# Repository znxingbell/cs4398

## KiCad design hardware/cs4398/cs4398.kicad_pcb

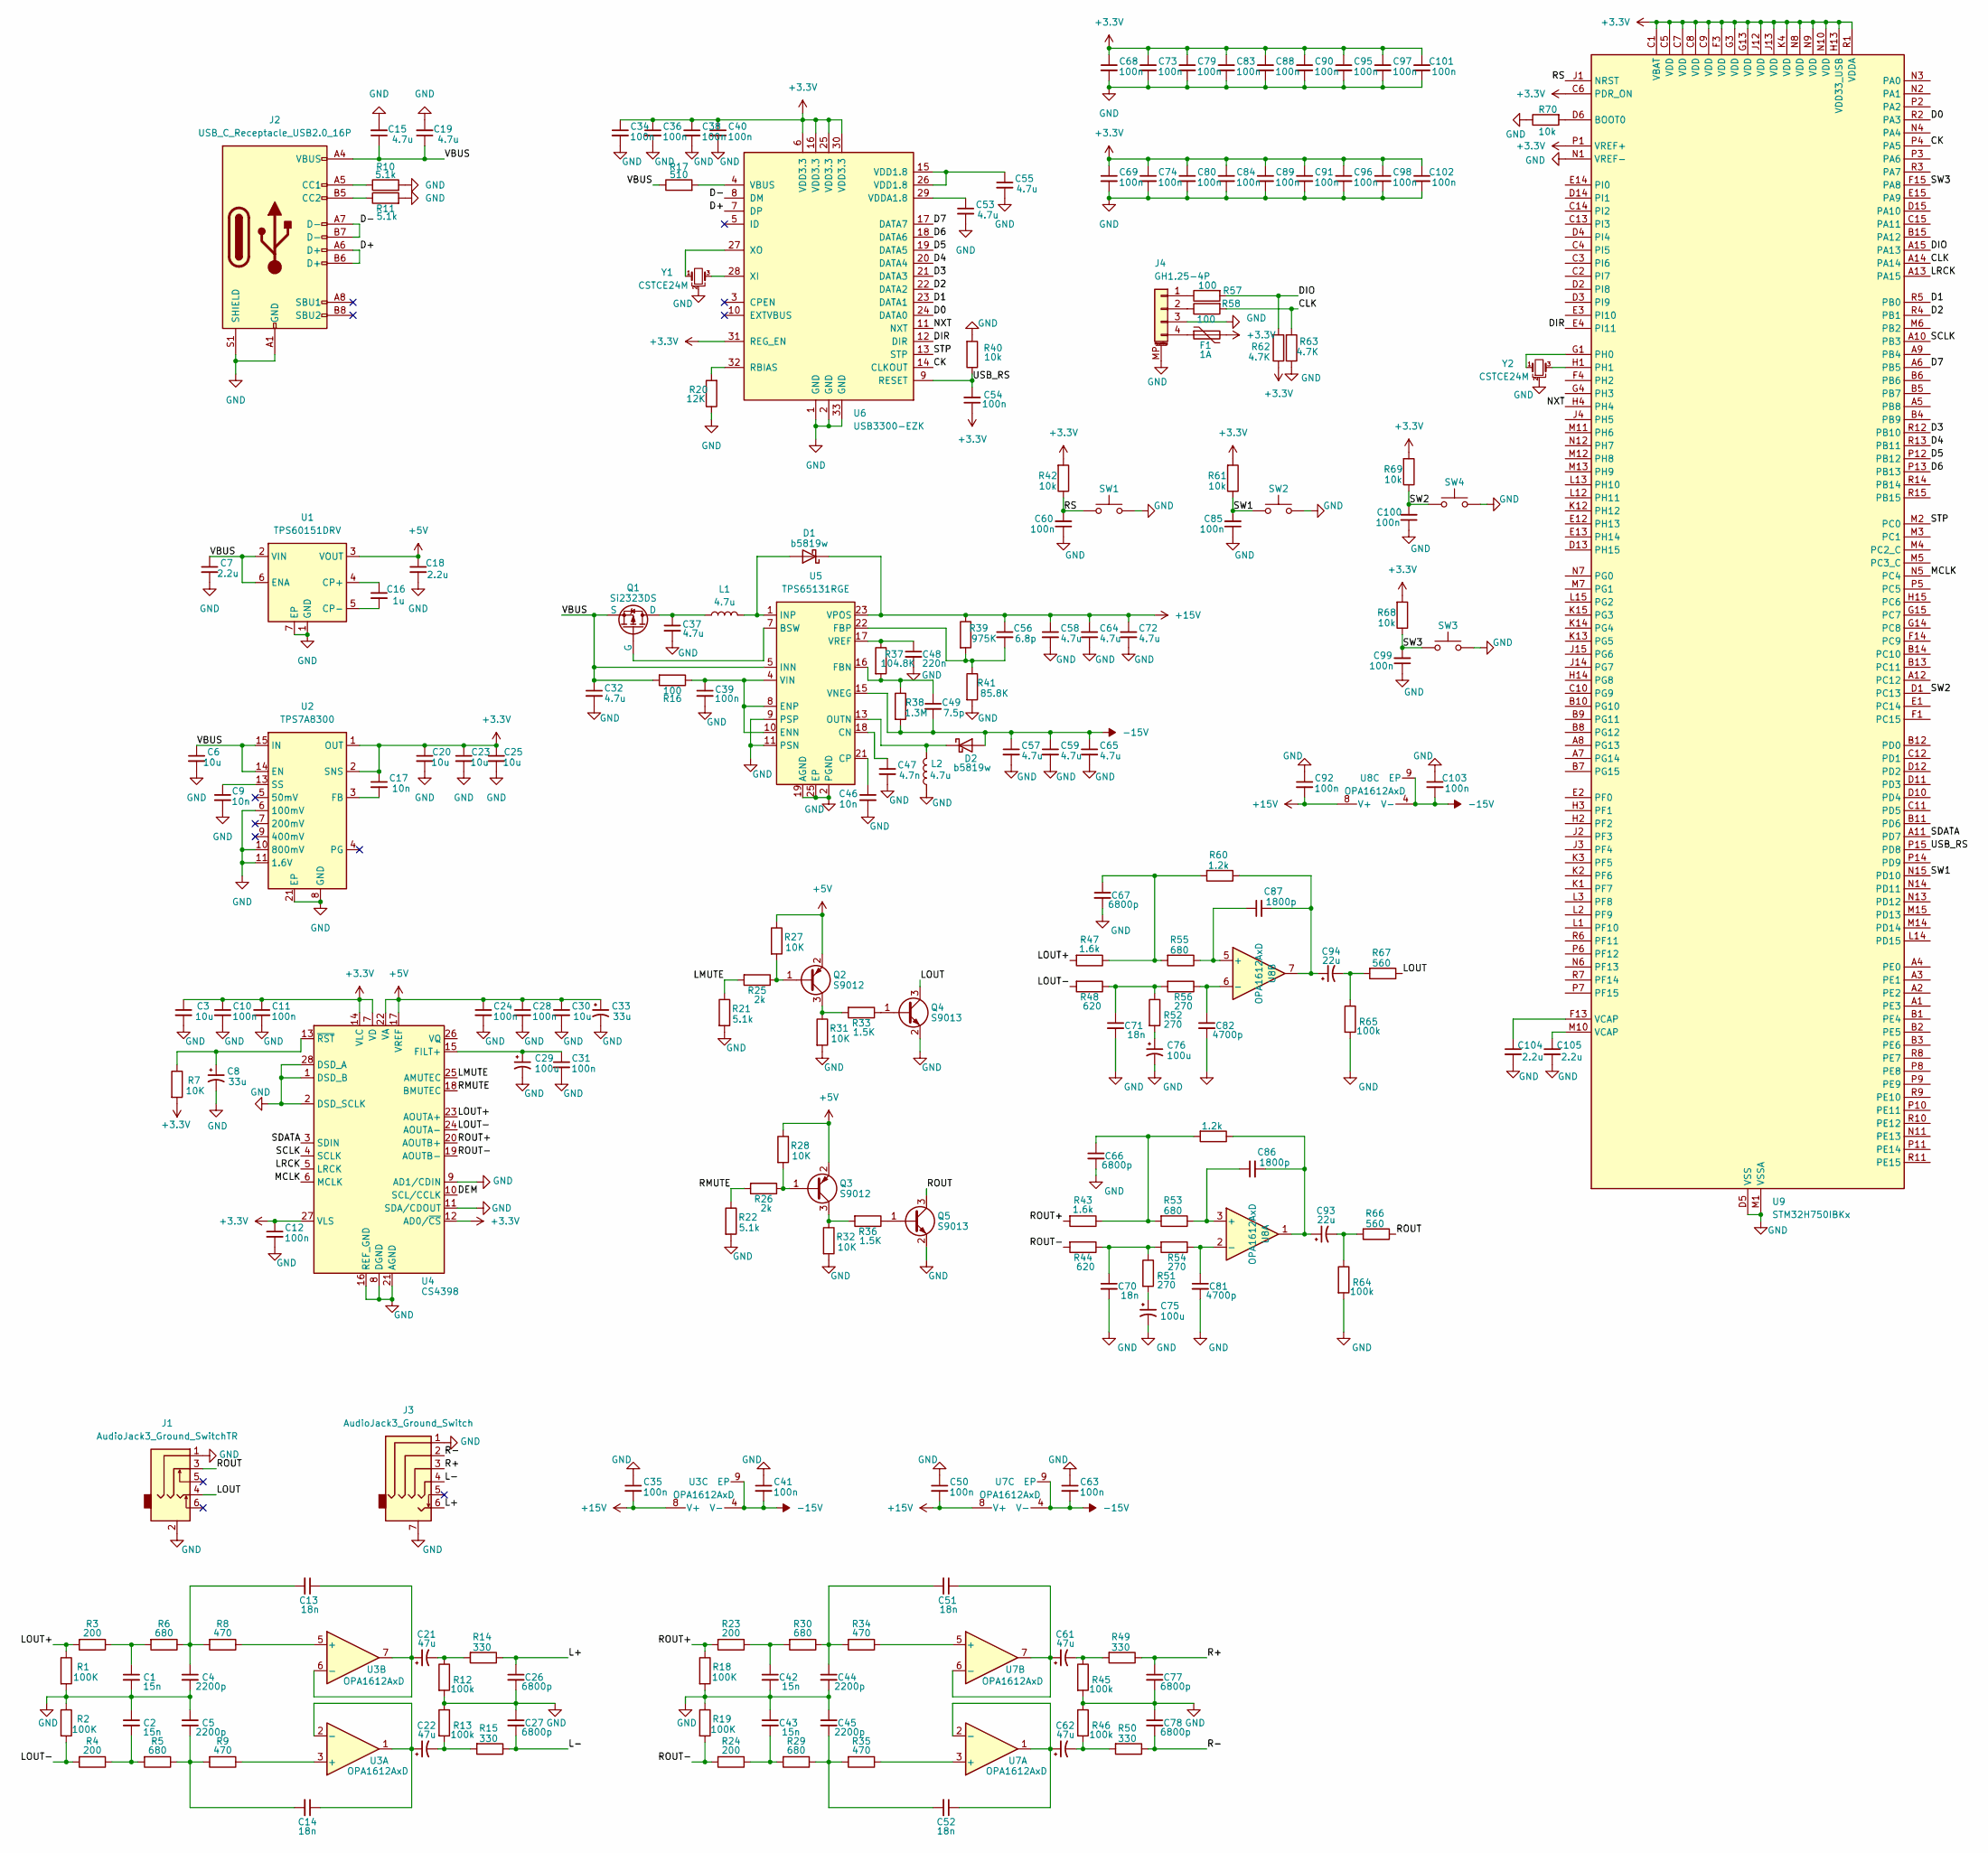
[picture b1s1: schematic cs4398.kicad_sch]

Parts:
C1, C2, C42, C43: 15n; C_0402_1005Metric
C3, C6, C20, C23, C25, C30: 10u; C_0805_2012Metric
C4, C5, C44, C45: 2200p; C_0402_1005Metric
C7, C18, C104, C105: 2.2u; C_0402_1005Metric
C8, C33: 33u; CP_EIA-3528-15_AVX-H
C9, C17, C46: 10n; C_0402_1005Metric
C10, C11, C12, C24, C28, C31, C34, C35, C36, C38, C39, C40, C41, C50, C63, C68, C69, C73, C74, C79, C80, C83, C84, C88, C89, C90, C91, C92, C95, C96, C97, C98, C101, C102, C103: 100n; C_0402_1005Metric
C13, C14, C51, C52, C70, C71: 18n; C_0402_1005Metric
C15, C19, C53, C55: 4.7u; C_0603_1608Metric
C16: 1u; C_0402_1005Metric
C21, C22, C61, C62: 47u; CP_EIA-3528-15_AVX-H
C26, C27, C66, C67, C77, C78: 6800p; C_0402_1005Metric
C29, C75, C76: 100u; CP_EIA-3528-15_AVX-H
C32, C37, C57, C58, C59, C64, C65, C72: 4.7u; C_0805_2012Metric
C47: 4.7n; C_0402_1005Metric
C48: 220n; C_0402_1005Metric
C49: 7.5p; C_0402_1005Metric
C54, C60, C85, C99, C100: 100n; C_0603_1608Metric
C56: 6.8p; C_0402_1005Metric
C81, C82: 4700p; C_0402_1005Metric
C86, C87: 1800p; C_0402_1005Metric
C93, C94: 22u; CP_EIA-3528-15_AVX-H
D1, D2: b5819w; D_SOD-123
F1: 1A; Fuse_0603_1608Metric
J1: AudioJack3_Ground_SwitchTR; Jack_3.5mm_PJ311_Horizontal
J2: USB_C_Receptacle_USB2.0_16P; USB_C_Receptacle_GCT_USB4105-xx-A_16P_TopMnt_Horizontal
J3: AudioJack3_Ground_Switch; Jack_6.35mm_Neutrik_NSJ12HH-1_Horizontal
J4: GH1.25-4P; JST_GH_BM04B-GHS-TBT_1x04-1MP_P1.25mm_Vertical
L1, L2: 4.7u; L_APV_APH0420
Q1: Si2323DS; SOT-23
Q2, Q3: S9012; SOT-23
Q4, Q5: S9013; SOT-23
R1, R2, R18, R19: 100K; R_0402_1005Metric
R3, R4, R23, R24: 200; R_0402_1005Metric
R5, R6, R29, R30, R53, R55: 680; R_0402_1005Metric
R7, R27, R28, R31, R32: 10K; R_0402_1005Metric
R8, R9, R34, R35: 470; R_0402_1005Metric
R10, R11, R21, R22: 5.1k; R_0402_1005Metric
R12, R13, R45, R46, R64, R65: 100k; R_0402_1005Metric
R14, R15, R49, R50: 330; R_0402_1005Metric
R16: 100; R_0402_1005Metric
R17: 510; R_0402_1005Metric
R20: 12K; R_0402_1005Metric
R25, R26: 2k; R_0402_1005Metric
R33, R36: 1.5K; R_0402_1005Metric
R37: 104.8K; R_0402_1005Metric
R38: 1.3M; R_0402_1005Metric
R39: 975K; R_0402_1005Metric
R40, R42, R61, R68, R69: 10k; R_0603_1608Metric
R41: 85.8K; R_0402_1005Metric
R43, R47: 1.6k; R_0402_1005Metric
R44, R48: 620; R_0402_1005Metric
R51, R52, R54, R56: 270; R_0402_1005Metric
R57, R58: 100; R_0603_1608Metric
R59, R60: 1.2k; R_0402_1005Metric
R62, R63: 4.7K; R_0603_1608Metric
R66, R67: 560; R_0402_1005Metric
R70: 10k; R_0402_1005Metric
SW1, SW2, SW3, SW4: SW_Omron_B3FS; SW_SPST_TS-1088-xR025
U1: TPS60151DRV; WSON-6-1EP_2x2mm_P0.65mm_EP1x1.6mm_ThermalVias
U2: TPS7A8300; QFN-20-1EP_3.5x3.5mm_P0.5mm_EP2x2mm_ThermalVias
U3, U7, U8: OPA1612AxD; WSON-8-1EP_3x3mm_P0.5mm_EP1.2x2mm_ThermalVias
U4: CS4398; TSSOP-28_4.4x9.7mm_P0.65mm
U5: TPS65131RGE; VQFN-24-1EP_4x4mm_P0.5mm_EP2.45x2.45mm_ThermalVias
U6: USB3300-EZK; QFN-32-1EP_5x5mm_P0.5mm_EP3.45x3.45mm
U9: STM32H750IBKx; UFBGA-201_10x10mm_Layout15x15_P0.65mm
Y1, Y2: CSTCE24M; Resonator_SMD_Murata_CSTxExxV-3Pin_3.0x1.1mm

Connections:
+3.3V: C3.1, C10.1, C11.1, C12.1, C17.1, C20.1, C23.1, C25.1, C34.1, C36.1, C38.1, C40.1, C54.1, C68.1, C69.1, C73.1, C74.1, C79.1, C80.1, C83.1, C84.1, C88.1, C89.1, C90.1, C91.1, C95.1, C96.1, C97.1, C98.1, C101.1, C102.1, F1.2, R7.2, R42.2, R61.2, R62.1, R68.2, R69.2, U2.1 (OUT), U2.2 (SNS), U2.19 (OUT), U2.20 (OUT), U4.7 (VD), U4.12 (AD0/~CS), U4.14 (VLC), U4.27 (VLS), U6.6 (VDD3.3), U6.16 (VDD3.3), U6.25 (VDD3.3), U6.30 (VDD3.3), U6.31 (REG_EN), U9.C1 (VBAT), U9.C5 (VDD), U9.C6 (PDR_ON), U9.C7 (VDD), U9.C8 (VDD), U9.C9 (VDD), U9.F3 (VDD), U9.G3 (VDD), U9.G13 (VDD), U9.H13 (VDD33_USB), U9.J12 (VDD), U9.J13 (VDD), U9.K4 (VDD), U9.N8 (VDD), U9.N9 (VDD), U9.N10 (VDD), U9.P1 (VREF+), U9.R1 (VDDA)
+5V: C18.1, C24.1, C28.1, C30.1, C33.1, Q2.2 (E), Q3.2 (E), R27.1, R28.1, U1.3 (VOUT), U4.17 (VREF), U4.22 (VA)
+15V: C35.2, C50.2, C56.1, C58.1, C64.1, C72.1, C92.2, D1.1 (K), R39.1, U3.8 (V+), U5.23 (VPOS), U7.8 (V+), U8.8 (V+)
-15V: C41.2, C49.2, C57.1, C59.1, C63.2, C65.1, C103.2, D2.2 (A), R38.2, U3.4 (V-), U3.9 (EP), U5.15 (VNEG), U7.4 (V-), U7.9 (EP), U8.4 (V-), U8.9 (EP)
/CK: U6.14 (CLKOUT), U9.P4 (PA5)
/CLK: R58.2, R63.2, U9.A14
/D0: U6.24 (DATA0), U9.R2 (PA3)
/D1: U6.23 (DATA1), U9.R5 (PB0)
/D2: U6.22 (DATA2), U9.R4 (PB1)
/D3: U6.21 (DATA3), U9.R12 (PB10)
/D4: U6.20 (DATA4), U9.R13 (PB11)
/D5: U6.19 (DATA5), U9.P12 (PB12)
/D6: U6.18 (DATA6), U9.P13 (PB13)
/D7: U6.17 (DATA7), U9.A6 (PB5)
/D+: J2.A6 (D+), J2.B6 (D+), U6.7 (DP)
/D-: J2.A7 (D-), J2.B7 (D-), U6.8 (DM)
/DEM: U4.10 (SCL/CCLK)
/DIO: R57.2, R62.2, U9.A15 (PA13)
/DIR: U6.12 (DIR), U9.E4 (PI11)
/L+: C26.1, J3.6, R14.1
/L-: C27.2, J3.4, R15.1
/LMUTE: R21.1, R25.2, U4.25 (AMUTEC)
/LOUT: J1.4, Q4.3 (C), R67.1
/LOUT+: R1.1, R3.2, R47.2, U4.23 (AOUTA+)
/LOUT-: R2.2, R4.2, R48.2, U4.24 (AOUTA-)
/LRCK: U4.5 (LRCK), U9.A13 (PA15)
/MCLK: U4.6 (MCLK), U9.N5 (PC4)
/NXT: U6.11 (NXT), U9.H4
/R+: C77.1, J3.3, R49.1
/R-: C78.2, J3.2, R50.1
/RMUTE: R22.1, R26.2, U4.18 (BMUTEC)
/ROUT: J1.3, Q5.3 (C), R66.1
/ROUT+: R18.1, R23.2, R43.2, U4.20 (AOUTB+)
/ROUT-: R19.2, R24.2, R44.2, U4.19 (AOUTB-)
/RS: C60.2, R42.1, SW1.1, U9.J1 (NRST)
/SCLK: U4.4 (SCLK), U9.A10 (PB3)
/SDATA: U4.3 (SDIN), U9.A11 (PD7)
/STP: U6.13 (STP), U9.M2 (PC0)
/SW1: C85.2, R61.1, SW2.1, U9.N15 (PD10)
/SW2: C100.2, R69.1, SW4.1, U9.D1 (PC13)
/SW3: C99.2, R68.1, SW3.1, U9.F15 (PA8)
/USB_RS: C54.2, R40.1, U6.9 (RESET), U9.P15 (PD8)
/VBUS: C6.1, C7.1, C15.1, C19.1, C32.1, J2.A4 (VBUS), J2.A9 (VBUS), J2.B4 (VBUS), J2.B9 (VBUS), Q1.2 (S), R16.2, R17.1, U1.2 (VIN), U1.6 (ENA), U2.14 (EN), U2.15 (IN), U2.16 (IN), U2.17 (IN), U5.5 (INN), U5.6 (INN)
GND: C1.2, C2.1, C3.2, C4.2, C5.1, C6.2, C7.2, C8.2, C9.2, C10.2, C11.2, C12.2, C15.2, C18.2, C19.2, C20.2, C23.2, C24.2, C25.2, C26.2, C27.1, C28.2, C29.2, C30.2, C31.2, C32.2, C33.2, C34.2, C35.1, C36.2, C37.2, C38.2, C39.2, C40.2, C41.1, C42.2, C43.1, C44.2, C45.1, C46.2, C47.2, C48.2, C50.1, C53.2, C55.2, C57.2, C58.2, C59.2, C60.1, C63.1, C64.2, C65.2, C66.2, C67.2, C68.2, C69.2, C70.2, C71.2, C72.2, C73.2, C74.2, C75.2, C76.2, C77.2, C78.1, C79.2, C80.2, C81.2, C82.2, C83.2, C84.2, C85.1, C88.2, C89.2, C90.2, C91.2, C92.1, C95.2, C96.2, C97.2, C98.2, C99.1, C100.1, C101.2, C102.2, C103.1, C104.2, C105.2, J1.1, J1.2, J2.A1 (GND), J2.A12 (GND), J2.B1 (GND), J2.B12 (GND), J2.S1 (SHIELD), J3.1, J3.7, J4.3, J4.MP (MountPin), L2.1, Q4.2 (E), Q5.2 (E), R1.2, R2.1, R10.2, R11.2, R12.2, R13.1, R18.2, R19.1, R20.1, R21.2, R22.2, R31.2, R32.2, R40.2, R41.2, R45.2, R46.1, R63.1, R64.2, R65.2, R70.1, SW1.2, SW2.2, SW3.2, SW4.2, U1.1 (GND), U1.7 (EP), U2.6 (100mV), U2.8 (GND), U2.10 (800mV), U2.11 (1.6V), U2.18 (GND), U2.21 (EP), U4.1 (DSD_B), U4.2 (DSD_SCLK), U4.8 (DGND), U4.9 (AD1/CDIN), U4.11 (SDA/CDOUT), U4.16 (REF_GND), U4.21 (AGND), U4.28 (DSD_A), U5.2 (PGND), U5.3 (PGND), U5.9 (PSP), U5.11 (PSN), U5.19 (AGND), U5.25 (EP), U6.1 (GND), U6.2 (GND), U6.33 (GND), U9.D5 (VSS), U9.D7 (VSS), U9.D8 (VSS), U9.D9 (VSS), U9.F2 (VSS), U9.F6 (VSS), U9.F7 (VSS), U9.F8 (VSS), U9.F9 (VSS), U9.F10 (VSS), U9.F12 (VSS), U9.G2 (VSS), U9.G6 (VSS), U9.G7 (VSS), U9.G8 (VSS), U9.G9 (VSS), U9.G10 (VSS), U9.G12 (VSS), U9.H6 (VSS), U9.H7 (VSS), U9.H8 (VSS), U9.H9 (VSS), U9.H10 (VSS), U9.H12 (VSS), U9.J6 (VSS), U9.J7 (VSS), U9.J8 (VSS), U9.J9 (VSS), U9.J10 (VSS), U9.K6 (VSS), U9.K7 (VSS), U9.K8 (VSS), U9.K9 (VSS), U9.K10 (VSS), U9.L4 (VSS), U9.M1 (VSSA), U9.M8 (VSS), U9.M9 (VSS), U9.N1 (VREF-), Y1.2, Y2.2
unnamed: C1.1, R3.1, R6.2
unnamed: C2.2, R4.1, R5.2
unnamed: C4.1, C13.2, R6.1, R8.2
unnamed: C5.2, C14.2, R5.1, R9.2
unnamed: C21.2, R12.1, R14.2
unnamed: C22.2, R13.2, R15.2
unnamed: C42.1, R23.1, R30.2
unnamed: C43.2, R24.1, R29.2
unnamed: C44.1, C51.2, R30.1, R34.2
unnamed: C45.2, C52.2, R29.1, R35.2
unnamed: C55.1, U6.15 (VDD1.8), U6.26 (VDD1.8)
unnamed: C61.2, R45.1, R49.2
unnamed: C62.2, R46.2, R50.2
unnamed: C66.1, R43.1, R53.2, R59.2
unnamed: C67.1, R47.1, R55.2, R60.2
unnamed: C70.1, R44.1, R51.1, R54.2
unnamed: C71.1, R48.1, R52.1, R56.2
unnamed: C75.1, R51.2
unnamed: C76.1, R52.2
unnamed: C86.2, C93.1, R59.1, U8.1
unnamed: C87.2, C94.1, R60.1, U8.7
unnamed: C93.2, R64.1, R66.2
unnamed: C94.2, R65.1, R67.2
unnamed: C104.1, U9.F13 (VCAP)
unnamed: C105.1, U9.M10 (VCAP)
unnamed: D1.2 (A), L1.2, U5.1 (INP), U5.24 (INP)
unnamed: D2.1 (K), L2.2, U5.13 (OUTN), U5.14 (OUTN)
unnamed: J2.A5 (CC1), R10.1
unnamed: J2.B5 (CC2), R11.1
unnamed: J4.1, R57.1
unnamed: J4.2, R58.1
unnamed: F1.1, J4.4
unnamed: C37.1, L1.1, Q1.3 (D)
unnamed: Q1.1 (G), U5.7 (BSW)
unnamed: Q2.1 (B), R25.1, R27.2
unnamed: Q2.3 (C), R31.1, R33.2
unnamed: Q3.1 (B), R26.1, R28.2
unnamed: Q3.3 (C), R32.1, R36.2
unnamed: Q4.1 (B), R33.1
unnamed: Q5.1 (B), R36.1
unnamed: C16.1, U1.4 (CP+)
unnamed: C16.2, U1.5 (CP-)
unnamed: C17.2, U2.3 (FB)
unnamed: C9.1, U2.13 (SS)
unnamed: R9.1, U3.3 (+)
unnamed: C14.1, C22.1, U3.1, U3.2 (-)
unnamed: R8.1, U3.5 (+)
unnamed: C13.1, C21.1, U3.6 (-), U3.7
unnamed: C29.1, C31.1, U4.15 (FILT+)
unnamed: C8.1, R7.1, U4.13 (~RST)
unnamed: C47.1, U5.18 (CN)
unnamed: C46.1, U5.21 (CP)
unnamed: C39.1, R16.1, U5.4 (VIN), U5.8 (ENP), U5.10 (ENN)
unnamed: C49.1, R37.2, R38.1, U5.16 (FBN)
unnamed: C56.2, R39.2, R41.1, U5.22 (FBP)
unnamed: C48.1, R37.1, U5.17 (VREF)
unnamed: R20.2, U6.32 (RBIAS)
unnamed: R17.2, U6.4 (VBUS)
unnamed: C53.1, U6.29 (VDDA1.8)
unnamed: U6.28 (XI), Y1.3
unnamed: U6.27 (XO), Y1.1
unnamed: R35.1, U7.3 (+)
unnamed: C52.1, C62.1, U7.1, U7.2 (-)
unnamed: R34.1, U7.5 (+)
unnamed: C51.1, C61.1, U7.6 (-), U7.7
unnamed: C86.1, R53.1, U8.3 (+)
unnamed: C81.1, R54.1, U8.2 (-)
unnamed: C87.1, R55.1, U8.5 (+)
unnamed: C82.1, R56.1, U8.6 (-)
unnamed: R70.2, U9.D6 (BOOT0)
unnamed: U9.G1 (PH0), Y2.1
unnamed: U9.H1, Y2.3

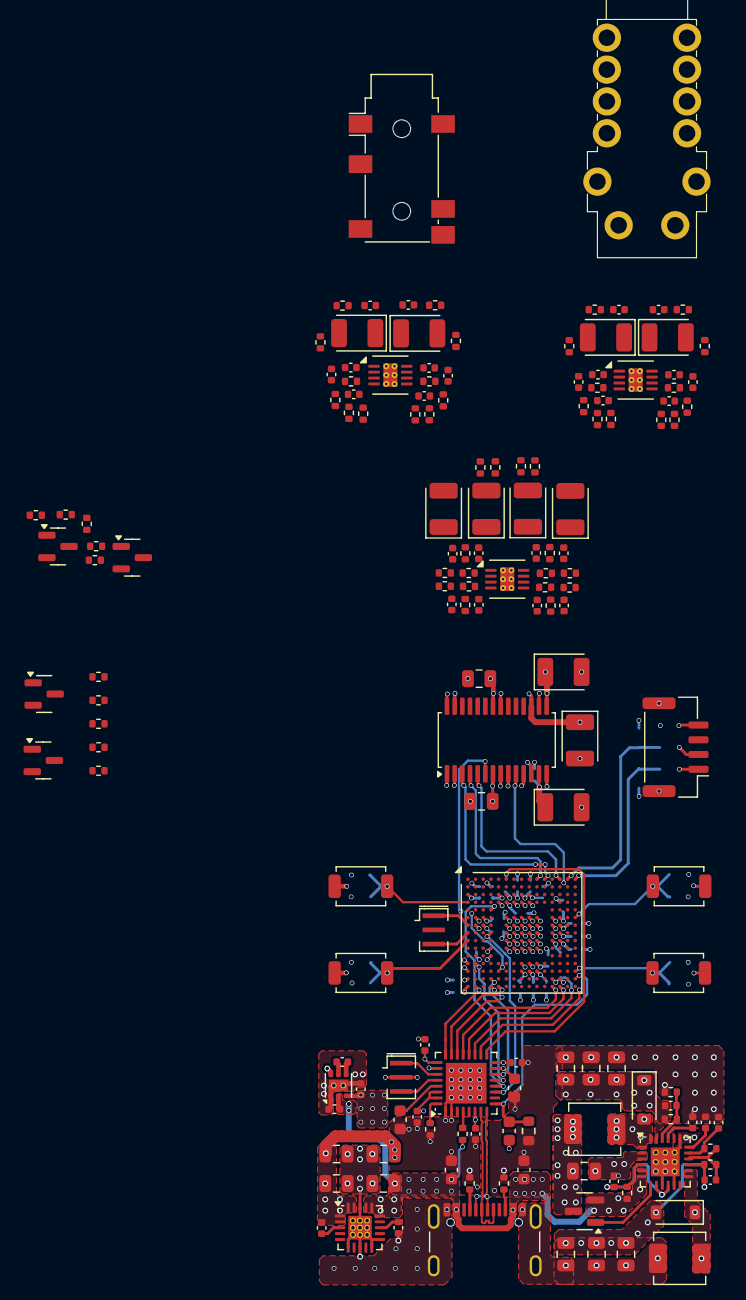
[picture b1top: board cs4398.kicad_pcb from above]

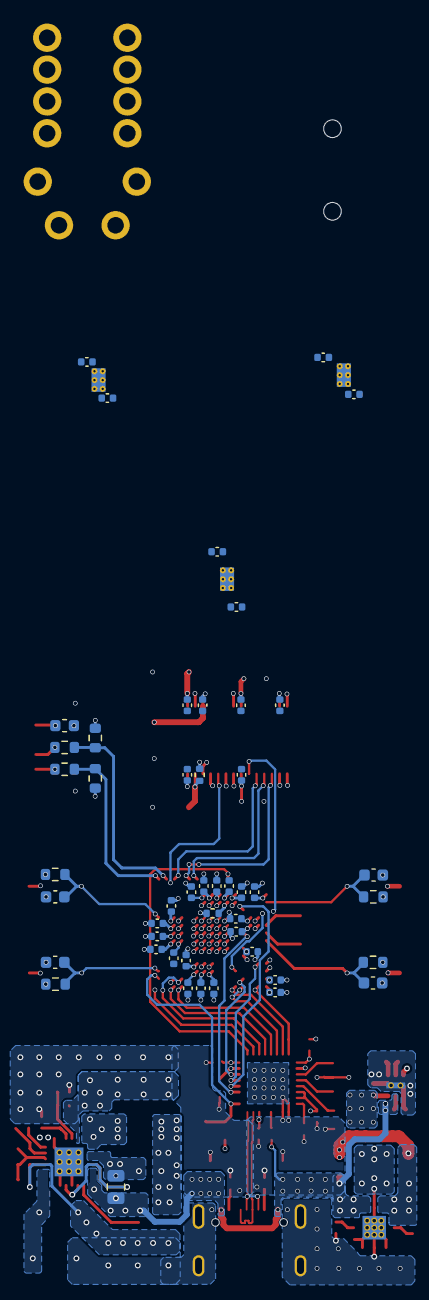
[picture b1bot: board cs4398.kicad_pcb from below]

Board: 4 copper layers, 204 parts (48 on the bottom side), 115 nets.

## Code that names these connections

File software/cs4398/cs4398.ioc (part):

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Mcu.Name=STM32H750IBKx
Mcu.Package=UFBGA176+25
Mcu.UserName=STM32H750IBKx
PA13\ (JTMS/SWDIO).Mode=Serial_Wire
PA13\ (JTMS/SWDIO).Signal=DEBUG_JTMS-SWDIO
PA14\ (JTCK/SWCLK).Mode=Serial_Wire
PA14\ (JTCK/SWCLK).Signal=DEBUG_JTCK-SWCLK
PA15\ (JTDI).Mode=Half_Duplex_Master_Tx
PA15\ (JTDI).Signal=I2S1_WS
PA3.Mode=Device_HS
PA3.Signal=USB_OTG_HS_ULPI_D0
PA5.Mode=Device_HS
PA5.Signal=USB_OTG_HS_ULPI_CK
PB0.Mode=Device_HS
PB0.Signal=USB_OTG_HS_ULPI_D1
PB1.Mode=Device_HS
PB1.Signal=USB_OTG_HS_ULPI_D2
PB10.Mode=Device_HS
PB10.Signal=USB_OTG_HS_ULPI_D3
PB11.Mode=Device_HS
PB11.Signal=USB_OTG_HS_ULPI_D4
PB12.Mode=Device_HS
PB12.Signal=USB_OTG_HS_ULPI_D5
PB13.Mode=Device_HS
PB13.Signal=USB_OTG_HS_ULPI_D6
PB3\ (JTDO/TRACESWO).Mode=Half_Duplex_Master_Tx
PB3\ (JTDO/TRACESWO).Signal=I2S1_CK
PB5.Mode=Device_HS
PB5.Signal=USB_OTG_HS_ULPI_D7
PC0.Mode=Device_HS
PC0.Signal=USB_OTG_HS_ULPI_STP
PC4.Mode=Master_Clock_Activated
PC4.Signal=I2S1_MCK
PD7.Mode=Half_Duplex_Master_Tx
PD7.Signal=I2S1_SDO
PH0-OSC_IN\ (PH0).Mode=HSE-External-Oscillator
PH0-OSC_IN\ (PH0).Signal=RCC_OSC_IN
PH1-OSC_OUT\ (PH1).Mode=HSE-External-Oscillator
PH1-OSC_OUT\ (PH1).Signal=RCC_OSC_OUT
PH4.Mode=Device_HS
PH4.Signal=USB_OTG_HS_ULPI_NXT
PI11.Mode=Device_HS
PI11.Signal=USB_OTG_HS_ULPI_DIR
RCC.HSE_VALUE=24000000
RCC.SYSCLKFreq_VALUE=180000000
RCC.SYSCLKSource=RCC_SYSCLKSOURCE_PLLCLK
board=custom

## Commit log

2025-09-09 sync 9.9
2025-09-15 sync 9.15
2025-09-18 添加4.4mm平衡输出
